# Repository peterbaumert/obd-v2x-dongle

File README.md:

# obd-v2x-dongle

Hobby OBD-II plug-in dongle that reads vehicle data, receives ITS-G5 (802.11p) V2X messages and uploads everything over LTE.

> **Receive-only for ITS-G5.** Transmitting on the 5.9 GHz ITS band requires EN 302 571 compliant equipment (or an experimental licence from the Bundesnetzagentur). This project does not transmit V2X messages.

## Architecture

```
OBD-II J1962 plug
 ├─ pin 16 (+12 V) ──► reverse-polarity + TVS (ISO 7637 / 16750) ──► 3 A buck ──► 3.8 V (LTE)  ──► 3.3 V LDO (logic)
 ├─ pin 6/14 (CAN) ──► CAN transceiver ──► ESP32-C5 TWAI
 ├─ pin 7 (K-Line) ──► K-Line transceiver ──► ESP32-C5 UART
 └─ pin 4/5 (GND)

ESP32-C5-WROOM-1U ── u.FL ──► 5.9 GHz antenna   (ITS-G5 RX via esphome-its-g5, BLE for setup)
        │ UART
Quectel EC200U-EU (LTE Cat 1 + GNSS) ── LTE main + GNSS antennas (U.FL), nano-SIM
```

### Power management
- Ignition detection (supply > ~13.2 V or CAN activity) to sleep the modem when parked
- Low-battery cutoff (~11.8 V) to avoid draining the car battery
- Cranking ride-through down to ~6 V

## PCB (fully routed, DRC clean; manufacturing review pending)

52 x 65 mm (plus the OBD plug in front), 4 layers, parts on both sides. Top: power, LTE modem, U.FL antennas. Bottom: CAN/K-Line, ESP32-C5, SIM, USB-C.

Design review and open decisions: [`docs/design-review.md`](docs/design-review.md).

## Repo layout

| Path | Contents |
|---|---|
| `hardware/` | KiCad 10 project (schematic, PCB) |
| `firmware/` | ESP32-C5 firmware (planned) |
| `docs/` | Datasheets notes, design decisions |

## Related

- [esphome-its-g5](https://github.com/peterbaumert/esphome-its-g5) — ESP32-C5 ITS-G5 receiver component

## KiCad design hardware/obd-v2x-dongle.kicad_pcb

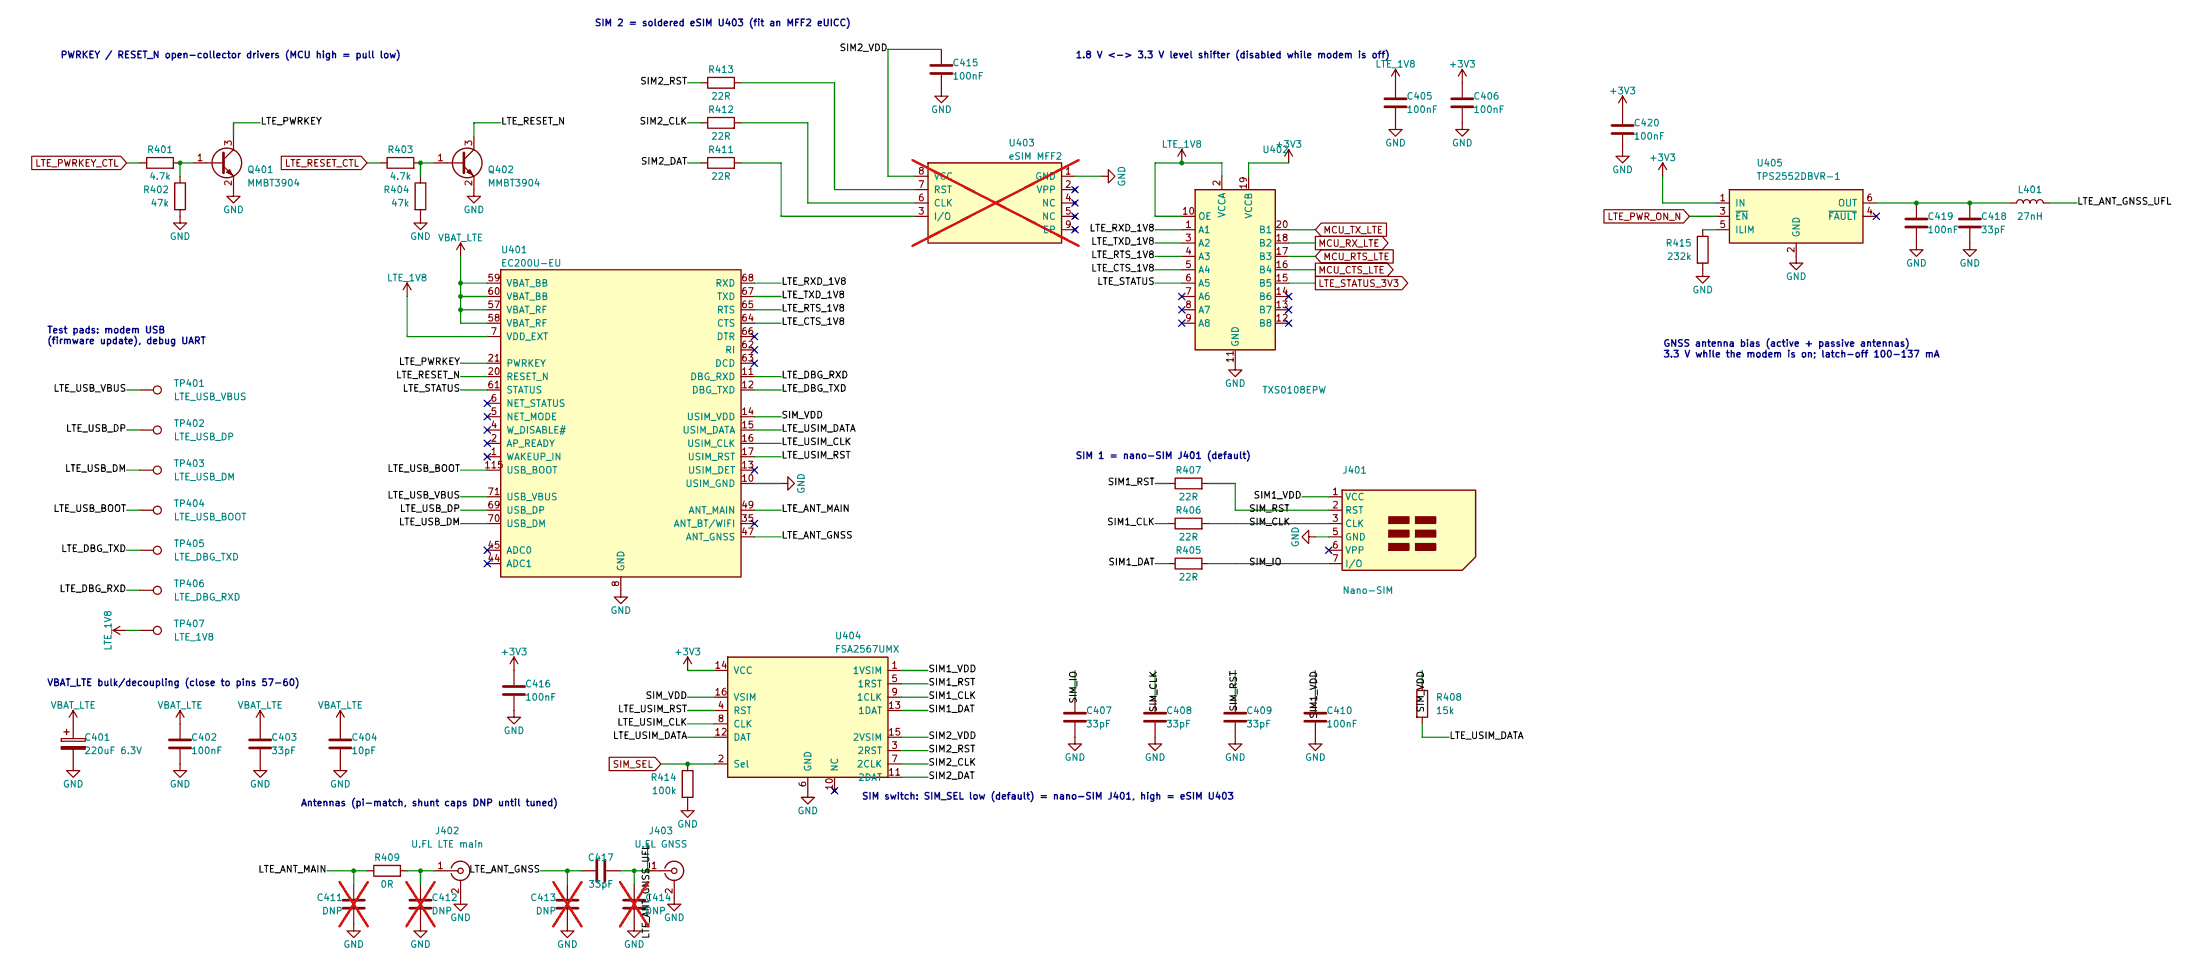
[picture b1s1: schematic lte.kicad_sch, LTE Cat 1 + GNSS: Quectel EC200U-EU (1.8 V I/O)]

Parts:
C401: 220uF 6.3V; CP_EIA-7343-31_Kemet-D; MPN T495D227K006ATE100; LCSC C2798131
C402, C405, C406: 100nF; C_0603_1608Metric
C403, C407, C408, C409: 33pF; C_0402_1005Metric
C404: 10pF; C_0402_1005Metric
C410, C415, C416, C419, C420: 100nF; C_0402_1005Metric
C411, C412, C413, C414: DNP; C_0402_1005Metric; not fitted
C417, C418: 33pF; C_0402_1005Metric; MPN 0402CG330J500NT; LCSC C1562
J401: Nano-SIM; nanoSIM_GCT_SIM8060-6-0-14-00; MPN SIM8060-6-0-14-00-A; LCSC C6296715
J402: U.FL LTE main; U.FL_Hirose_U.FL-R-SMT-1_Vertical; MPN U.FL-R-SMT-1(10); LCSC C88373
J403: U.FL GNSS; U.FL_Hirose_U.FL-R-SMT-1_Vertical; MPN U.FL-R-SMT-1(10); LCSC C88373
L401: 27nH; L_0402_1005Metric; MPN LQG15HS27NJ02D; LCSC C12669
Q401, Q402: MMBT3904; SOT-23; MPN MMBT3904; LCSC C20526
R401, R403: 4.7k; R_0603_1608Metric
R402, R404: 47k; R_0603_1608Metric
R405, R406, R407, R411, R412, R413: 22R; R_0402_1005Metric
R408: 15k; R_0402_1005Metric
R409: 0R; R_0402_1005Metric
R414: 100k; R_0402_1005Metric
R415: 232k; R_0402_1005Metric
TP401: LTE_USB_VBUS; TestPoint_Pad_D1.0mm
TP402: LTE_USB_DP; TestPoint_Pad_D1.0mm
TP403: LTE_USB_DM; TestPoint_Pad_D1.0mm
TP404: LTE_USB_BOOT; TestPoint_Pad_D1.0mm
TP405: LTE_DBG_TXD; TestPoint_Pad_D1.0mm
TP406: LTE_DBG_RXD; TestPoint_Pad_D1.0mm
TP407: LTE_1V8; TestPoint_Pad_D1.0mm
U401: EC200U-EU; Quectel_EC200U; MPN EC200UEUAA-N05-SGNSA; LCSC C2942341
U402: TXS0108EPW; TSSOP-20_4.4x6.5mm_P0.65mm; MPN TXS0108EPWR; LCSC C17206
U403: eSIM MFF2; WSON-8-1EP_6x5mm_P1.27mm_EP3.4x4mm; MPN MFF2 eSIM, optional (DNP); not fitted
U404: FSA2567UMX; UQFN-16_1.8x2.6mm_P0.4mm; MPN FSA2567UMX; LCSC C357761
U405: TPS2552DBVR-1; SOT-23-6; MPN TPS2552DBVR-1; LCSC C140331

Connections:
+3V3: C406.1, C416.1, C420.1, U402.19 (VCCB), U404.14 (VCC), U405.1 (IN); also elsewhere on the board
/LTE + GNSS (EC200U)/LTE_ANT_GNSS: C413.1, C417.1, U401.47 (ANT_GNSS)
/LTE + GNSS (EC200U)/LTE_ANT_GNSS_UFL: C414.1, C417.2, J403.1 (In), L401.2
/LTE + GNSS (EC200U)/LTE_ANT_MAIN: C411.1, R409.1, U401.49 (ANT_MAIN)
/LTE + GNSS (EC200U)/LTE_CTS_1V8: U401.64 (CTS), U402.5 (A4)
/LTE + GNSS (EC200U)/LTE_DBG_RXD: TP406.1, U401.11 (DBG_RXD)
/LTE + GNSS (EC200U)/LTE_DBG_TXD: TP405.1, U401.12 (DBG_TXD)
/LTE + GNSS (EC200U)/LTE_PWRKEY: Q401.3 (C), U401.21 (PWRKEY)
/LTE + GNSS (EC200U)/LTE_RESET_N: Q402.3 (C), U401.20 (RESET_N)
/LTE + GNSS (EC200U)/LTE_RTS_1V8: U401.65 (RTS), U402.4 (A3)
/LTE + GNSS (EC200U)/LTE_RXD_1V8: U401.68 (RXD), U402.1 (A1)
/LTE + GNSS (EC200U)/LTE_STATUS: U401.61 (STATUS), U402.6 (A5)
/LTE + GNSS (EC200U)/LTE_TXD_1V8: U401.67 (TXD), U402.3 (A2)
/LTE + GNSS (EC200U)/LTE_USB_BOOT: TP404.1, U401.115 (USB_BOOT)
/LTE + GNSS (EC200U)/LTE_USB_DM: TP403.1, U401.70 (USB_DM)
/LTE + GNSS (EC200U)/LTE_USB_DP: TP402.1, U401.69 (USB_DP)
/LTE + GNSS (EC200U)/LTE_USB_VBUS: TP401.1, U401.71 (USB_VBUS)
/LTE + GNSS (EC200U)/LTE_USIM_CLK: U401.16 (USIM_CLK), U404.8 (CLK)
/LTE + GNSS (EC200U)/LTE_USIM_DATA: R408.2, U401.15 (USIM_DATA), U404.12 (DAT)
/LTE + GNSS (EC200U)/LTE_USIM_RST: U401.17 (USIM_RST), U404.4 (RST)
/LTE + GNSS (EC200U)/SIM1_CLK: R406.1, U404.9 (1CLK)
/LTE + GNSS (EC200U)/SIM1_DAT: R405.1, U404.13 (1DAT)
/LTE + GNSS (EC200U)/SIM1_RST: R407.1, U404.5 (1RST)
/LTE + GNSS (EC200U)/SIM1_VDD: C410.1, J401.1 (VCC), U404.1 (1VSIM)
/LTE + GNSS (EC200U)/SIM2_CLK: R412.1, U404.7 (2CLK)
/LTE + GNSS (EC200U)/SIM2_DAT: R411.1, U404.11 (2DAT)
/LTE + GNSS (EC200U)/SIM2_RST: R413.1, U404.3 (2RST)
/LTE + GNSS (EC200U)/SIM2_VDD: C415.1, U403.8 (VCC), U404.15 (2VSIM)
/LTE + GNSS (EC200U)/SIM_CLK: C408.1, J401.3 (CLK), R406.2
/LTE + GNSS (EC200U)/SIM_IO: C407.1, J401.7 (I/O), R405.2
/LTE + GNSS (EC200U)/SIM_RST: C409.1, J401.2 (RST), R407.2
/LTE + GNSS (EC200U)/SIM_VDD: R408.1, U401.14 (USIM_VDD), U404.16 (VSIM)
GND: C401.2, C402.2, C403.2, C404.2, C405.2, C406.2, C407.2, C408.2, C409.2, C410.2, C411.2, C412.2, C413.2, C414.2, C415.2, C416.2, C418.2, C419.2, C420.2, J401.5 (GND), J402.2 (Ext), J403.2 (Ext), Q401.2 (E), Q402.2 (E), R402.2, R404.2, R414.2, R415.2, U401.8 (GND), U401.9 (GND), U401.10 (USIM_GND), U401.19 (GND), U401.22 (GND), U401.36 (GND), U401.46 (GND), U401.48 (GND), U401.50 (GND), U401.51 (GND), U401.52 (GND), U401.53 (GND), U401.54 (GND), U401.56 (GND), U401.72 (GND), U401.76 (GND), U401.85 (GND), U401.86 (GND), U401.87 (GND), U401.88 (GND), U401.89 (GND), U401.90 (GND), U401.91 (GND), U401.92 (GND), U401.93 (GND), U401.94 (GND), U401.95 (GND), U401.96 (GND), U401.97 (GND), U401.98 (GND), U401.99 (GND), U401.100 (GND), U401.101 (GND), U401.102 (GND), U401.103 (GND), U401.104 (GND), U401.105 (GND), U401.106 (GND), U401.107 (GND), U401.108 (GND), U401.109 (GND), U401.110 (GND), U401.111 (GND), U401.112 (GND), U402.11 (GND), U403.1 (GND), U404.6 (GND), U405.2 (GND); also elsewhere on the board
LTE_1V8: C405.1, TP407.1, U401.7 (VDD_EXT), U402.2 (VCCA), U402.10 (OE)
LTE_PWRKEY_CTL: R401.1; also elsewhere on the board
LTE_PWR_ON_N: U405.3 (~EN); also elsewhere on the board
LTE_RESET_CTL: R403.1; also elsewhere on the board
LTE_STATUS_3V3: U402.15 (B5); also elsewhere on the board
MCU_CTS_LTE: U402.16 (B4); also elsewhere on the board
MCU_RTS_LTE: U402.17 (B3); also elsewhere on the board
MCU_RX_LTE: U402.18 (B2); also elsewhere on the board
MCU_TX_LTE: U402.20 (B1); also elsewhere on the board
unnamed: C412.1, J402.1 (In), R409.2
unnamed: Q401.1 (B), R401.2, R402.1
unnamed: Q402.1 (B), R403.2, R404.1
unnamed: R412.2, U403.6 (CLK)
unnamed: R411.2, U403.3 (I/O)
unnamed: R413.2, U403.7 (RST)
unnamed: R415.1, U405.5 (ILIM)
unnamed: C418.1, C419.1, L401.1, U405.6 (OUT)
SIM_SEL: R414.1, U404.2 (Sel); also elsewhere on the board
VBAT_LTE: C401.1, C402.1, C403.1, C404.1, U401.57 (VBAT_RF), U401.58 (VBAT_RF), U401.59 (VBAT_BB), U401.60 (VBAT_BB); also elsewhere on the board

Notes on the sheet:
SIM 1 = nano-SIM J401 (default)
PWRKEY / RESET_N open-collector drivers (MCU high = pull low)
Test pads: modem USB (firmware update), debug UART
VBAT_LTE bulk/decoupling (close to pins 57-60)
1.8 V <-> 3.3 V level shifter (disabled while modem is off)
Antennas (pi-match, shunt caps DNP until tuned)
GNSS antenna bias (active + passive antennas) 3.3 V while the modem is on; latch-off 100-137 mA
SIM switch: SIM_SEL low (default) = nano-SIM J401, high = eSIM U403
SIM 2 = soldered eSIM U403 (fit an MFF2 eUICC)

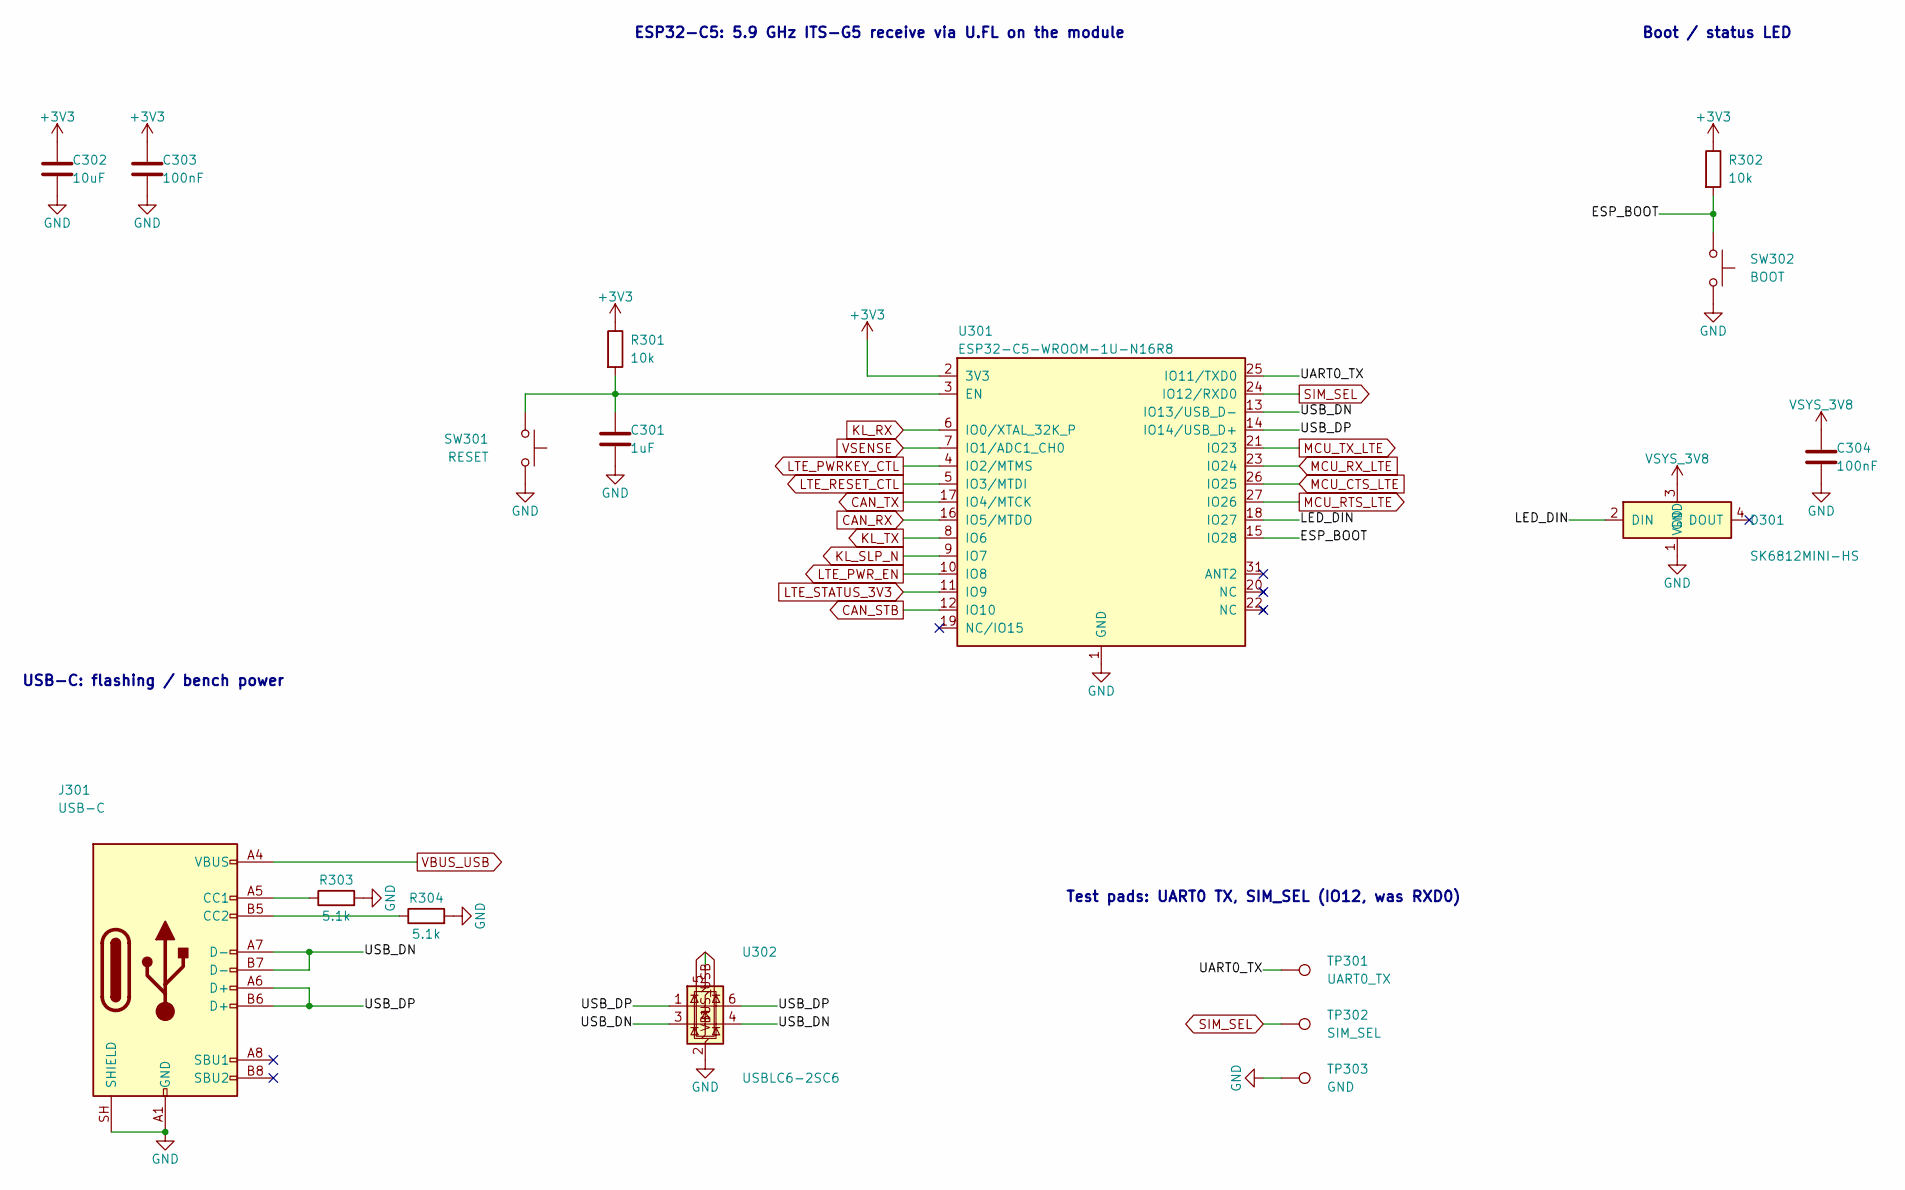
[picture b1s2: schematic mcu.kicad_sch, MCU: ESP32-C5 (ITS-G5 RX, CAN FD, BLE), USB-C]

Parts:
C301: 1uF; C_0603_1608Metric
C302: 10uF; C_0805_2012Metric
C303, C304: 100nF; C_0603_1608Metric
D301: SK6812MINI-HS; LED_SK6812MINI-HS_3.7x3.5mm; MPN SK6812MINI-HS; LCSC C2922787
J301: USB-C; USB_C_Receptacle_HRO_TYPE-C-31-M-12; MPN TYPE-C-31-M-12; LCSC C165948
R301, R302: 10k; R_0603_1608Metric
R303, R304: 5.1k; R_0603_1608Metric
SW301: RESET; SW_SPST_TL3342; MPN TL3342F450QG; LCSC C2886897
SW302: BOOT; SW_SPST_TL3342; MPN TL3342F450QG; LCSC C2886897
TP301: UART0_TX; TestPoint_Pad_D1.0mm
TP302: SIM_SEL; TestPoint_Pad_D1.0mm
TP303: GND; TestPoint_Pad_D1.0mm
U301: ESP32-C5-WROOM-1U-N16R8; ESP32-C5-WROOM-1U; MPN ESP32-C5-WROOM-1U-N16R8-V1.2; LCSC C54951857
U302: USBLC6-2SC6; SOT-23-6; MPN USBLC6-2SC6; LCSC C2827654

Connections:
+3V3: C302.1, C303.1, R301.1, R302.1, U301.2 (3V3); also elsewhere on the board
/MCU (ESP32-C5, USB)/ESP_BOOT: R302.2, SW302.1, U301.15 (IO28)
/MCU (ESP32-C5, USB)/LED_DIN: D301.2 (DIN), U301.18 (IO27)
/MCU (ESP32-C5, USB)/UART0_TX: TP301.1, U301.25 (IO11/TXD0)
/MCU (ESP32-C5, USB)/USB_DN: J301.A7 (D-), J301.B7 (D-), U301.13 (IO13/USB_D-), U302.3 (I/O2), U302.4 (I/O2)
/MCU (ESP32-C5, USB)/USB_DP: J301.A6 (D+), J301.B6 (D+), U301.14 (IO14/USB_D+), U302.1 (I/O1), U302.6 (I/O1)
CAN_RX: U301.16 (IO5/MTDO); also elsewhere on the board
CAN_STB: U301.12 (IO10); also elsewhere on the board
CAN_TX: U301.17 (IO4/MTCK); also elsewhere on the board
GND: C301.2, C302.2, C303.2, C304.2, D301.1 (GND), J301.A1 (GND), J301.A12 (GND), J301.B1 (GND), J301.B12 (GND), J301.SH (SHIELD), R303.2, R304.2, SW301.2, SW302.2, TP303.1, U301.1 (GND), U301.28 (GND), U301.29 (GND), U301.30 (GND), U301.32 (GND), U302.2 (GND); also elsewhere on the board
KL_RX: U301.6 (IO0/XTAL_32K_P); also elsewhere on the board
KL_SLP_N: U301.9 (IO7); also elsewhere on the board
KL_TX: U301.8 (IO6); also elsewhere on the board
LTE_PWRKEY_CTL: U301.4 (IO2/MTMS); also elsewhere on the board
LTE_PWR_EN: U301.10 (IO8); also elsewhere on the board
LTE_RESET_CTL: U301.5 (IO3/MTDI); also elsewhere on the board
LTE_STATUS_3V3: U301.11 (IO9); also elsewhere on the board
MCU_CTS_LTE: U301.26 (IO25); also elsewhere on the board
MCU_RTS_LTE: U301.27 (IO26); also elsewhere on the board
MCU_RX_LTE: U301.23 (IO24); also elsewhere on the board
MCU_TX_LTE: U301.21 (IO23); also elsewhere on the board
unnamed: J301.A5 (CC1), R303.1
unnamed: J301.B5 (CC2), R304.1
unnamed: C301.1, R301.2, SW301.1, U301.3 (EN)
SIM_SEL: TP302.1, U301.24 (IO12/RXD0); also elsewhere on the board
VBUS_USB: J301.A4 (VBUS), J301.A9 (VBUS), J301.B4 (VBUS), J301.B9 (VBUS), U302.5 (VBUS); also elsewhere on the board
VSENSE: U301.7 (IO1/ADC1_CH0); also elsewhere on the board
VSYS_3V8: C304.1, D301.3 (VDD); also elsewhere on the board

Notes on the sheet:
Test pads: UART0 TX, SIM_SEL (IO12, was RXD0)
USB-C: flashing / bench power
ESP32-C5: 5.9 GHz ITS-G5 receive via U.FL on the module
Boot / status LED

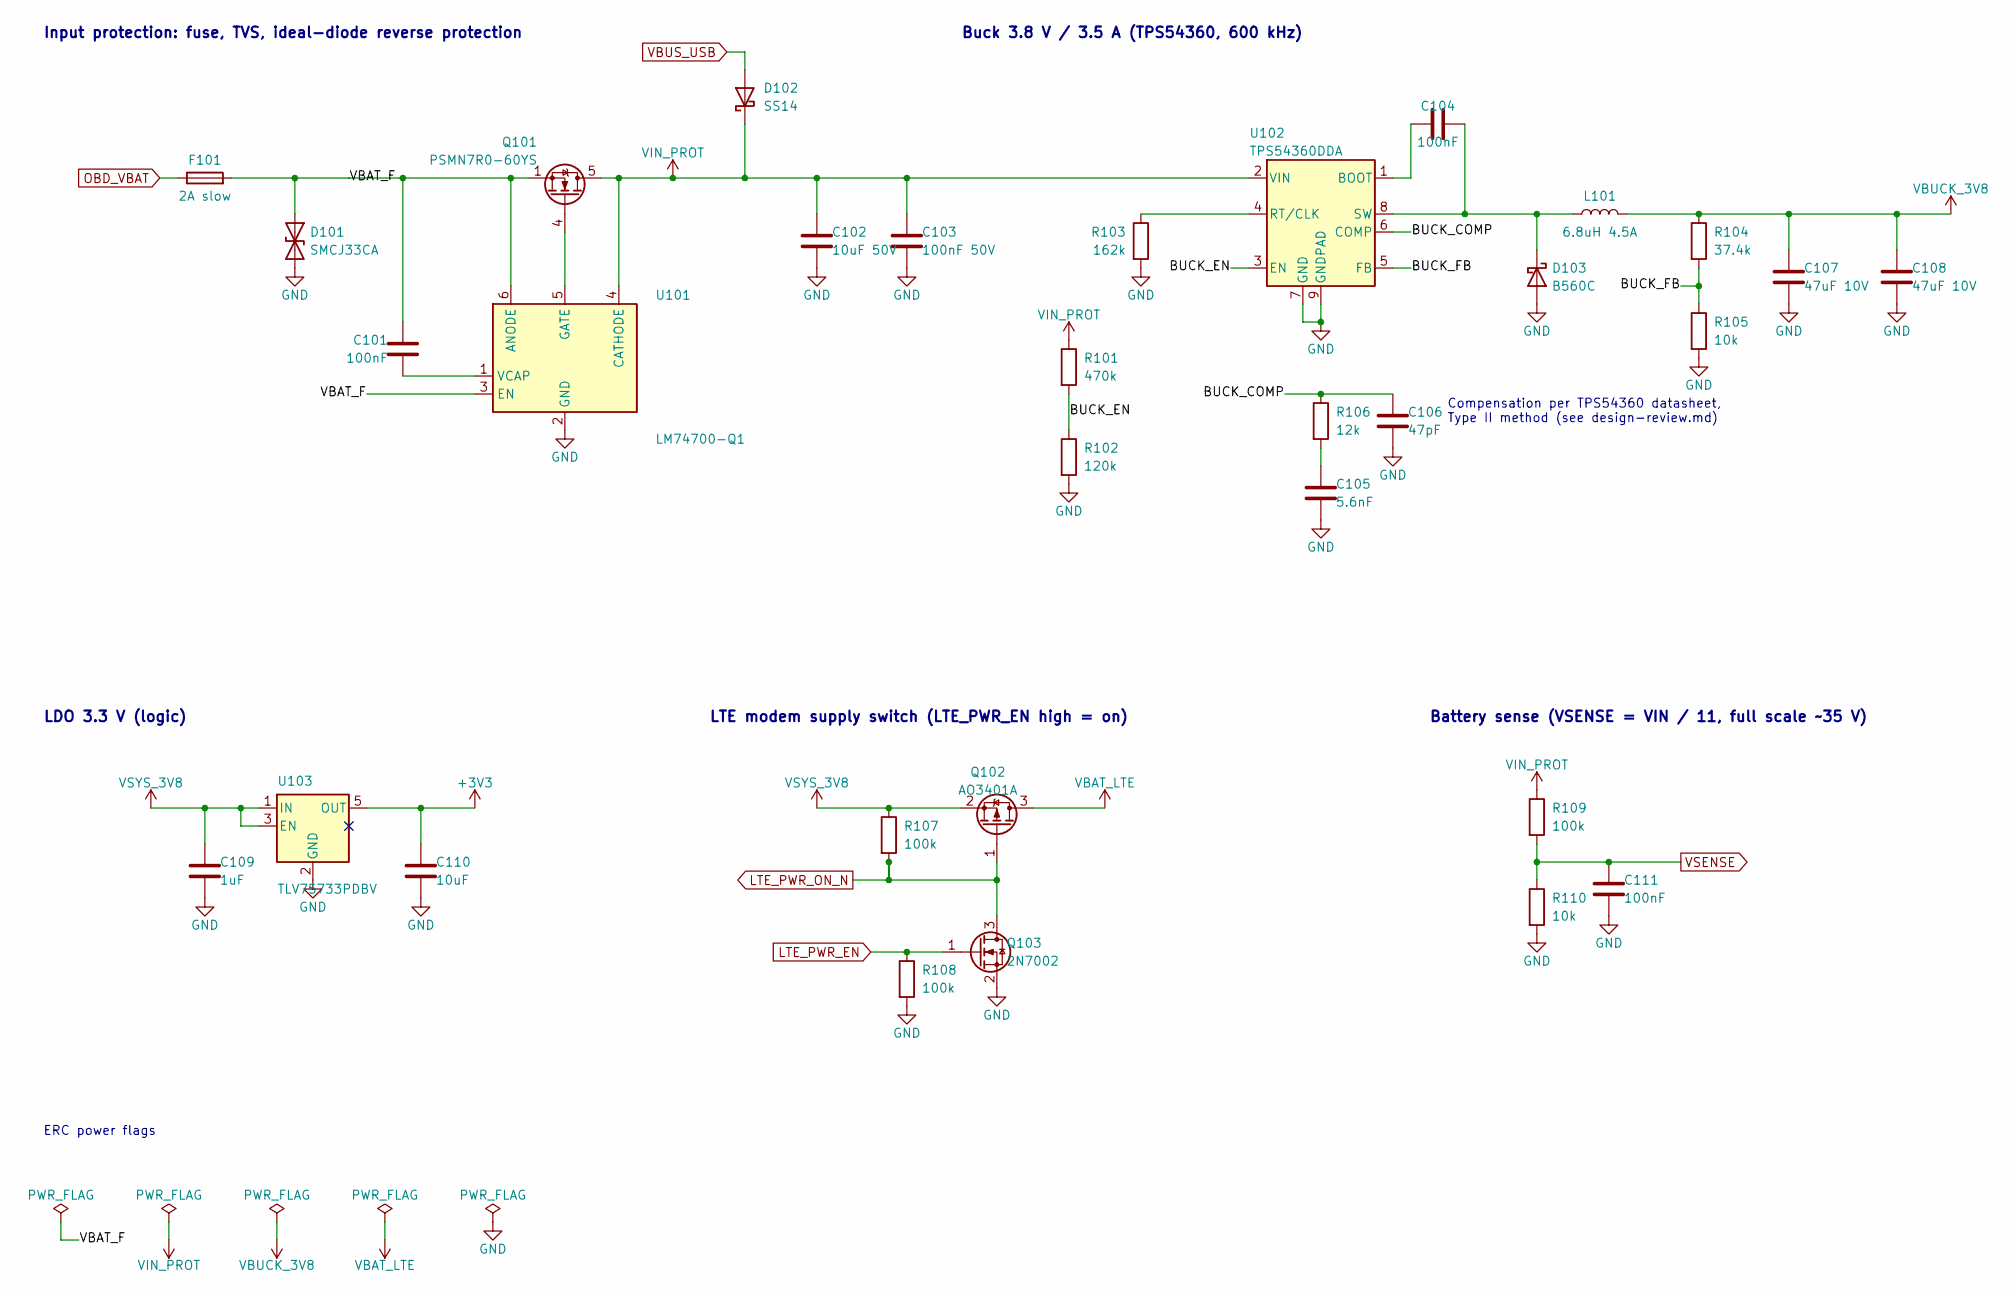
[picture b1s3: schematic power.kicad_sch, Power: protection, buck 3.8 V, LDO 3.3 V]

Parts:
C101, C104, C111: 100nF; C_0603_1608Metric
C102: 10uF 50V; C_1210_3225Metric
C103: 100nF 50V; C_0603_1608Metric
C105: 5.6nF; C_0603_1608Metric
C106: 47pF; C_0603_1608Metric
C107, C108: 47uF 10V; C_1210_3225Metric
C109: 1uF; C_0603_1608Metric
C110: 10uF; C_0805_2012Metric
D101: SMCJ33CA; D_SMC; MPN SMCJ33CA; LCSC C310048
D102: SS14; D_SMA; MPN SS14; LCSC C2480
D103: B560C; D_SMC; MPN B560C-13-F; LCSC C85100
F101: 2A slow; Fuse_1206_3216Metric; MPN 0466002.NRHF; LCSC C3105
L101: 6.8uH 4.5A; L_Sunlord_MWSA0605S; MPN MWSA0605S-6R8MT; LCSC C408466
Q101: PSMN7R0-60YS; LFPAK56; MPN PSMN7R0-60YS,115; LCSC C478143
Q102: AO3401A; SOT-23; MPN AO3401A; LCSC C15127
Q103: 2N7002; SOT-23; MPN 2N7002; LCSC C8545
R101: 470k; R_0603_1608Metric
R102: 120k; R_0603_1608Metric
R103: 162k; R_0603_1608Metric
R104: 37.4k; R_0603_1608Metric
R105, R110: 10k; R_0603_1608Metric
R106: 12k; R_0603_1608Metric
R107, R108, R109: 100k; R_0603_1608Metric
U101: LM74700-Q1; SOT-23-6; MPN LM74700QDBVRQ1; LCSC C2941042
U102: TPS54360DDA; TI_SO-PowerPAD-8_ThermalVias; MPN TPS54360DDAR; LCSC C44377
U103: TLV75733PDBV; SOT-23-5; MPN TLV75733PDBVR; LCSC C485517

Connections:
+3V3: C110.1, U103.5 (OUT); also elsewhere on the board
/Power/BUCK_COMP: C106.1, R106.1, U102.6 (COMP)
/Power/BUCK_EN: R101.2, R102.1, U102.3 (EN)
/Power/BUCK_FB: R104.2, R105.1, U102.5 (FB)
/Power/VBAT_F: C101.2, D101.1 (A1), F101.2, Q101.1 (S), Q101.2 (S), Q101.3 (S), U101.3 (EN), U101.6 (ANODE)
GND: C102.2, C103.2, C105.2, C106.2, C107.2, C108.2, C109.2, C110.2, C111.2, D101.2 (A2), D103.2 (A), Q103.2 (S), R102.2, R103.2, R105.2, R108.2, R110.2, U101.2 (GND), U102.7 (GND), U102.9 (GNDPAD), U103.2 (GND); also elsewhere on the board
LTE_PWR_EN: Q103.1 (G), R108.1; also elsewhere on the board
LTE_PWR_ON_N: Q102.1 (G), Q103.3 (D), R107.2; also elsewhere on the board
unnamed: C105.1, R106.2
unnamed: C104.2, D103.1 (K), L101.1, U102.8 (SW)
unnamed: Q101.4 (G), U101.5 (GATE)
unnamed: C101.1, U101.1 (VCAP)
unnamed: C104.1, U102.1 (BOOT)
unnamed: R103.1, U102.4 (RT/CLK)
OBD_VBAT: F101.1; also elsewhere on the board
VBAT_LTE: Q102.3 (D); also elsewhere on the board
VBUCK_3V8: C107.1, C108.1, L101.2, R104.1; also elsewhere on the board
VBUS_USB: D102.2 (A); also elsewhere on the board
VIN_PROT: C102.1, C103.1, D102.1 (K), Q101.5 (D), R101.1, R109.1, U101.4 (CATHODE), U102.2 (VIN); also elsewhere on the board
VSENSE: C111.1, R109.2, R110.1; also elsewhere on the board
VSYS_3V8: C109.1, Q102.2 (S), R107.1, U103.1 (IN), U103.3 (EN); also elsewhere on the board

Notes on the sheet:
LTE modem supply switch (LTE_PWR_EN high = on)
ERC power flags
Compensation per TPS54360 datasheet, Type II method (see design-review.md)
LDO 3.3 V (logic)
Buck 3.8 V / 3.5 A (TPS54360, 600 kHz)
Input protection: fuse, TVS, ideal-diode reverse protection
Battery sense (VSENSE = VIN / 11, full scale ~35 V)

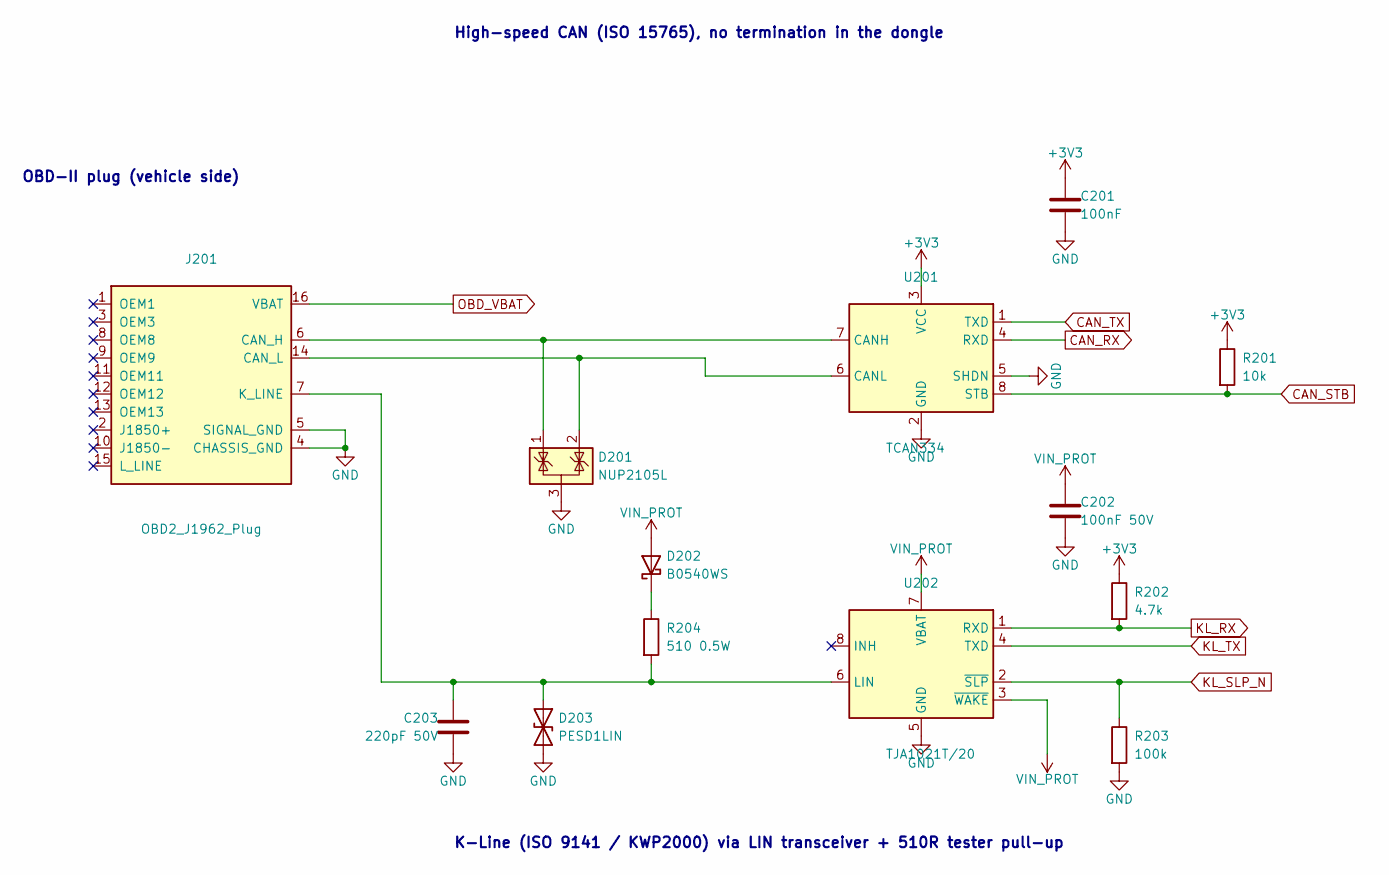
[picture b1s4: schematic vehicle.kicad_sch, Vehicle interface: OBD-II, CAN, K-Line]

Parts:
C201: 100nF; C_0603_1608Metric
C202: 100nF 50V; C_0603_1608Metric
C203: 220pF 50V; C_0603_1608Metric
D201: NUP2105L; SOT-23; MPN SZNUP2105LT1G; LCSC C233494
D202: B0540WS; D_SOD-323; MPN B0540WS-7; LCSC C52754523
D203: PESD1LIN; D_SOD-323; MPN PESD1LIN,115; LCSC C58901
J201: OBD2_J1962_Plug; OBD2_J1962_Plug_PCB; MPN CR-PG001 (OBD2 male 90deg PCB, hand-fit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
R201: 10k; R_0603_1608Metric
R202: 4.7k; R_0603_1608Metric
R203: 100k; R_0603_1608Metric
R204: 510 0.5W; R_1206_3216Metric
U201: TCAN334; SOIC-8_3.9x4.9mm_P1.27mm; MPN TCAN334DR; LCSC C2871143
U202: TJA1021T/20; SOIC-8_3.9x4.9mm_P1.27mm; MPN TJA1021T/20/CM,118; LCSC C128810

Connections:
+3V3: C201.1, R201.1, R202.1, U201.3 (VCC); also elsewhere on the board
CAN_RX: U201.4 (RXD); also elsewhere on the board
CAN_STB: R201.2, U201.8 (STB); also elsewhere on the board
CAN_TX: U201.1 (TXD); also elsewhere on the board
GND: C201.2, C202.2, C203.2, D201.3 (A), D203.2 (A2), J201.4 (CHASSIS_GND), J201.5 (SIGNAL_GND), R203.2, U201.2 (GND), U201.5 (SHDN), U202.5 (GND); also elsewhere on the board
KL_RX: R202.2, U202.1 (RXD); also elsewhere on the board
KL_SLP_N: R203.1, U202.2 (~SLP); also elsewhere on the board
KL_TX: U202.4 (TXD); also elsewhere on the board
unnamed: D202.1 (K), R204.1
unnamed: C203.1, D203.1 (A1), J201.7 (K_LINE), R204.2, U202.6 (LIN)
unnamed: D201.1 (K), J201.6 (CAN_H), U201.7 (CANH)
unnamed: D201.2 (K), J201.14 (CAN_L), U201.6 (CANL)
OBD_VBAT: J201.16 (VBAT); also elsewhere on the board
VIN_PROT: C202.1, D202.2 (A), U202.3 (~WAKE), U202.7 (VBAT); also elsewhere on the board

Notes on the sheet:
High-speed CAN (ISO 15765), no termination in the dongle
OBD-II plug (vehicle side)
K-Line (ISO 9141 / KWP2000) via LIN transceiver + 510R tester pull-up

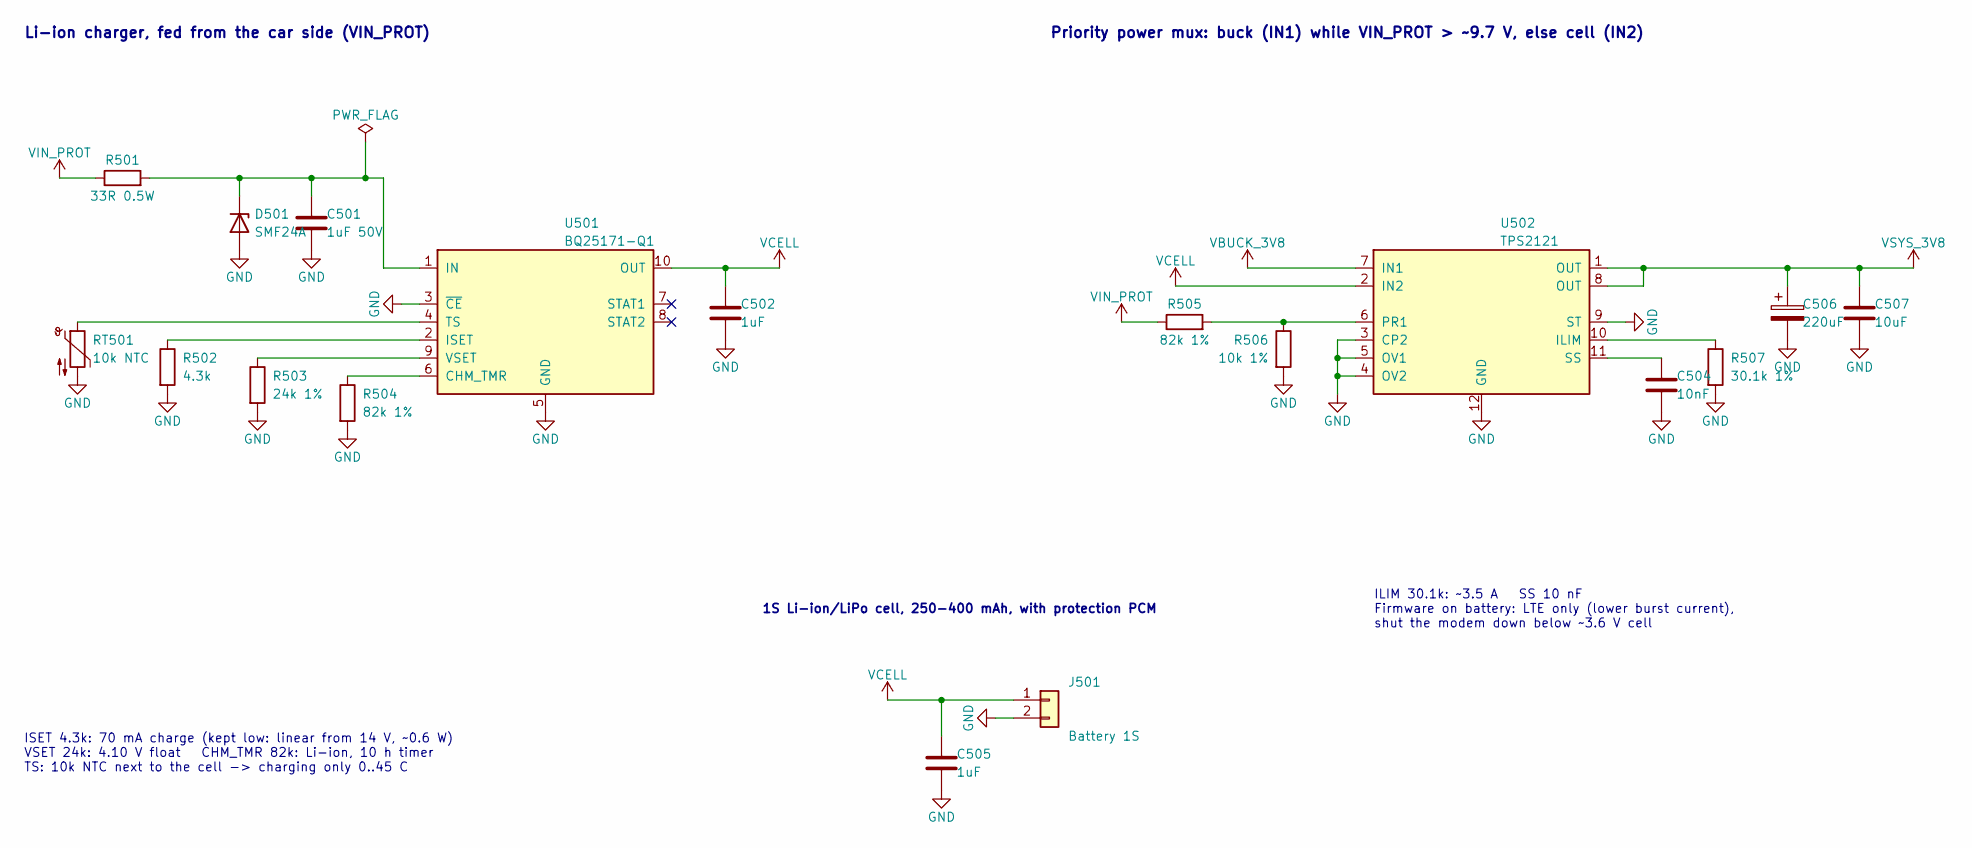
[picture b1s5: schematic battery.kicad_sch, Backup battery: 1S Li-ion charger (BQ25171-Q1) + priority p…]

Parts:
C501: 1uF 50V; C_0805_2012Metric
C502, C505: 1uF; C_0603_1608Metric
C504: 10nF; C_0603_1608Metric
C506: 220uF; CP_EIA-7343-31_Kemet-D; MPN T495D227K006ATE100; LCSC C2798131
C507: 10uF; C_0805_2012Metric
D501: SMF24A; D_SOD-123F; MPN SMF24A; LCSC C315999
J501: Battery 1S; JST_PH_B2B-PH-SM4-TB_1x02-1MP_P2.00mm_Vertical; MPN B2B-PH-SM4-TB(LF)(SN); LCSC C160352
R501: 33R 0.5W; R_1206_3216Metric
R502: 4.3k; R_0603_1608Metric
R503: 24k 1%; R_0603_1608Metric
R504, R505: 82k 1%; R_0603_1608Metric
R506: 10k 1%; R_0603_1608Metric
R507: 30.1k 1%; R_0603_1608Metric
RT501: 10k NTC; R_0603_1608Metric; MPN SDNT1608X103F3435FTF; LCSC C525660
U501: BQ25171-Q1; Texas_DRC0010J; MPN BQ25171QWDRCRQ1; LCSC C2861221
U502: TPS2121; Texas_VQFN-HR-12_2x2.5mm_P0.5mm; MPN TPS2121RUXR; LCSC C485916

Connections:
GND: C501.2, C502.2, C504.2, C505.2, C506.2, C507.2, D501.2 (A), J501.2, R502.2, R503.2, R504.2, R506.2, R507.2, RT501.2, U501.3 (~CE), U501.5 (GND), U501.11 (GND), U502.3 (CP2), U502.4 (OV2), U502.5 (OV1), U502.9 (ST), U502.12 (GND); also elsewhere on the board
unnamed: C501.1, D501.1 (K), R501.2, U501.1 (IN)
unnamed: R504.1, U501.6 (CHM_TMR)
unnamed: R502.1, U501.2 (ISET)
unnamed: RT501.1, U501.4 (TS)
unnamed: R503.1, U501.9 (VSET)
unnamed: R507.1, U502.10 (ILIM)
unnamed: R505.2, R506.1, U502.6 (PR1)
unnamed: C504.1, U502.11 (SS)
VBUCK_3V8: U502.7 (IN1); also elsewhere on the board
VCELL: C502.1, C505.1, J501.1, U501.10 (OUT), U502.2 (IN2)
VIN_PROT: R501.1, R505.1; also elsewhere on the board
VSYS_3V8: C506.1, C507.1, U502.1 (OUT), U502.8 (OUT); also elsewhere on the board

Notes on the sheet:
ILIM 30.1k: ~3.5 A SS 10 nF Firmware on battery: LTE only (lower burst current), shut the modem down below ~3.6 V cell
Li-ion charger, fed from the car side (VIN_PROT)
ISET 4.3k: 70 mA charge (kept low: linear from 14 V, ~0.6 W) VSET 24k: 4.10 V float CHM_TMR 82k: Li-ion, 10 h timer TS: 10k NTC next to the cell -> charging only 0..45 C
1S Li-ion/LiPo cell, 250-400 mAh, with protection PCM
Priority power mux: buck (IN1) while VIN_PROT > ~9.7 V, else cell (IN2)
